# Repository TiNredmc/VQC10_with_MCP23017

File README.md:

# VQC10_with_MCP23017
WIP(Work In Progress).Need help to coding to work with vqc 10.

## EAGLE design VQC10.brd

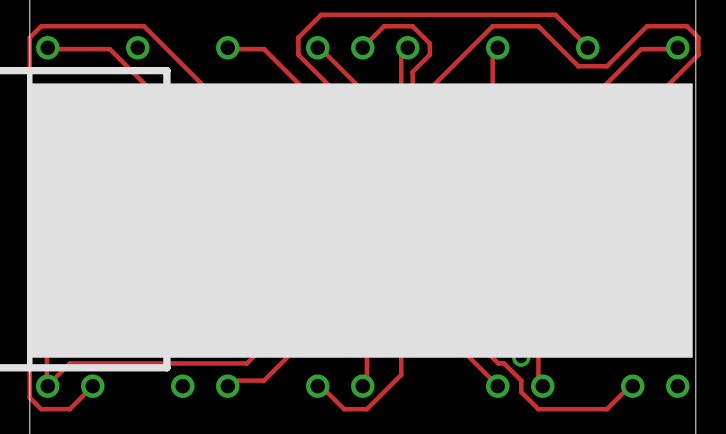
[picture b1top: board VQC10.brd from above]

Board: 2 copper layers, 3 parts (0 on the bottom side), 20 nets.

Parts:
E$1: 30DIP
E$2: SSOP28
E$3: 1X4MTA

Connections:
S$1: E$1.DO, E$2.28
S$2: E$1.D1, E$2.27
S$3: E$1.D2, E$2.26
S$4: E$1.D3, E$2.25
S$5: E$1.C1, E$2.24
S$6: E$1.C2, E$2.23
S$7: E$1.C3, E$2.22
S$8: E$1.C4, E$2.21
S$9: E$1.C5, E$2.1, E$2.18, E$3.1
S$10: E$1.R1, E$2.2
S$11: E$1.R2, E$2.3
S$12: E$1.R3, E$2.4
S$13: E$1.R4, E$2.5
S$14: E$1.R5, E$2.6
S$15: E$1.R6, E$2.7
S$16: E$1.R7, E$2.8
S$17: E$1.VCC, E$2.9
S$18: E$1.GND1, E$1.GND2, E$2.10, E$2.15, E$2.16, E$2.17, E$3.4
S$21: E$2.12, E$3.2
S$22: E$2.13, E$3.3

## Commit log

2017-11-26 schematic and driver board for VQC10
